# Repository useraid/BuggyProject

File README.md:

# Buggy Project (UTA024) TIET

The files for ECED part can be [found here.](empty)

The files for CSED part can be [found here.](empty)

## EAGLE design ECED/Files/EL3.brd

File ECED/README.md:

# ECED

## Labs

Lab 1 - [Reciever](https://github.com/useraid/BuggyProject/blob/main/ECED/Files/EL1.brd)

Lab 2 - [IR Module](https://github.com/useraid/BuggyProject/blob/main/ECED/Files/EL2.brd)

Lab 3 - [Transmitter](https://github.com/useraid/BuggyProject/blob/main/ECED/Files/EL3.brd)

## Challenges

[Bronze Challenge](./Bronze.ino)

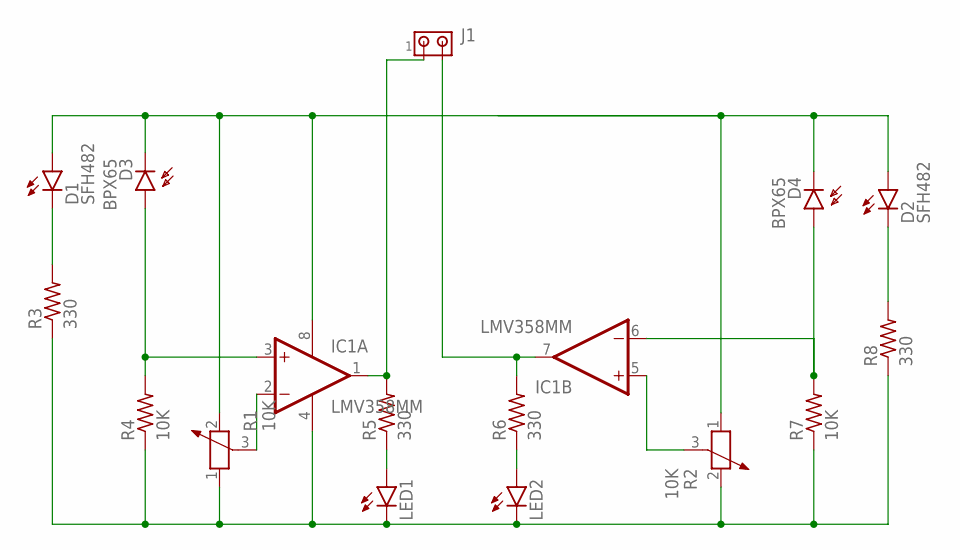
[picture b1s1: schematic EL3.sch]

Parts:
D1, D2: SFH482
D3, D4: BPX65
IC1: LMV358MM; MSOP08
J1: MTA02-100; 10X02MTA
LED1, LED2: LED3MM
R1, R2: 10K; PT-10
R3, R5, R6, R8: 330; 0204/5
R4, R7: 10K; 0204/5

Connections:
unnamed: LED2.A, R6.1
unnamed: IC1.4 (V-), LED1.K (C), LED2.K (C), R1.1, R2.2, R3.1, R4.1, R7.1, R8.1
unnamed: D4.A, IC1.6 (-IN), R7.2
unnamed: D2.K (C), R8.2
unnamed: D1.A, D2.A, D3.K (C), D4.K (C), IC1.8 (V+), R1.2, R2.1
unnamed: IC1.5 (+IN), R2.3
unnamed: IC1.7 (OUT), J1.2, R6.2
unnamed: IC1.1 (OUT), J1.1, R5.2
unnamed: LED1.A, R5.1
unnamed: D1.K (C), R3.2
unnamed: IC1.2 (-IN), R1.3
unnamed: D3.A, IC1.3 (+IN), R4.2

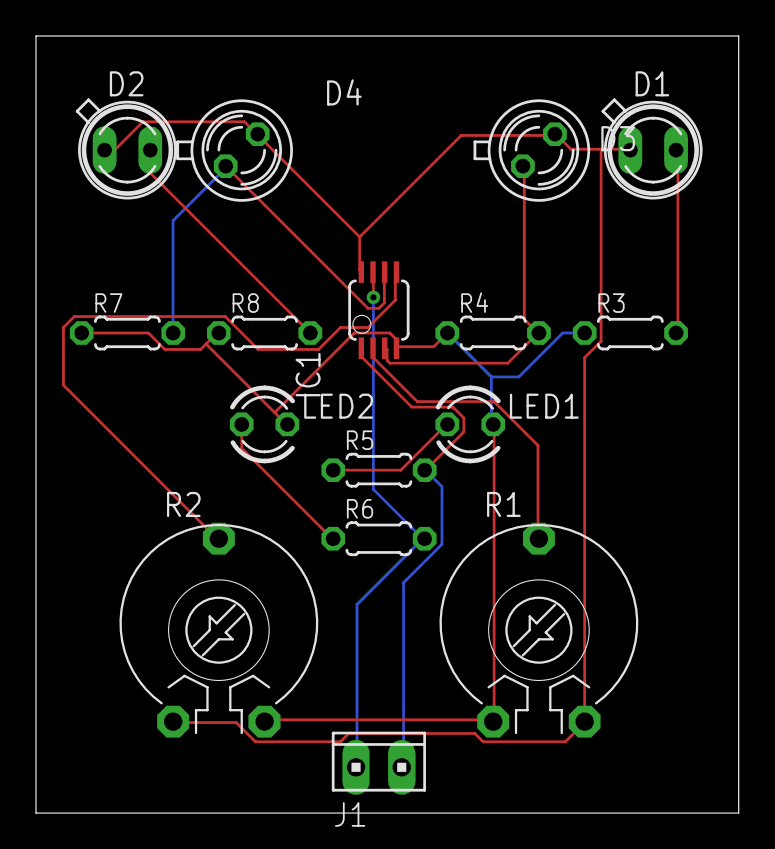
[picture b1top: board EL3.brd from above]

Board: 2 copper layers, 39.0 x 43.2 mm, 16 parts (0 on the bottom side), 12 nets.

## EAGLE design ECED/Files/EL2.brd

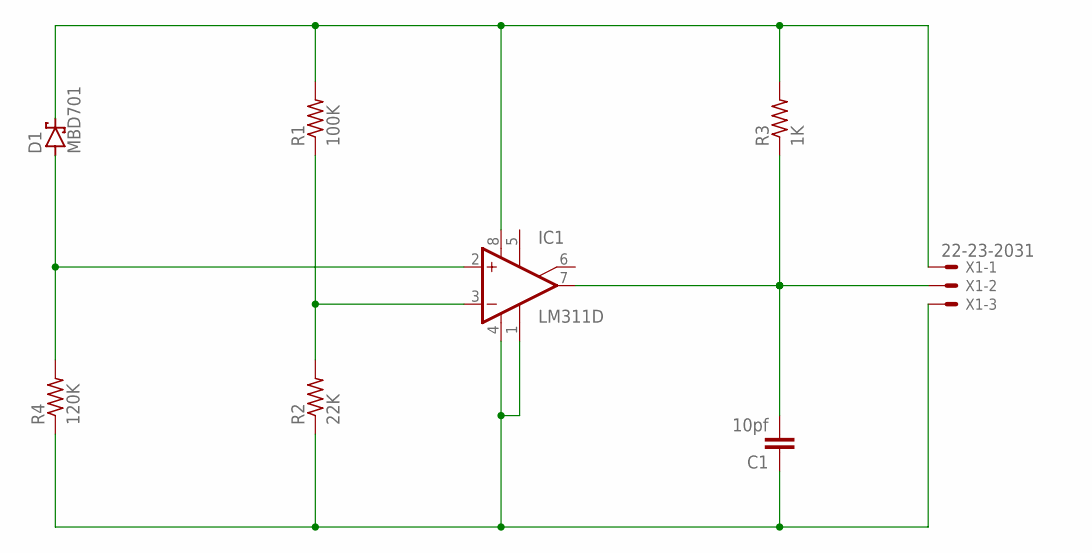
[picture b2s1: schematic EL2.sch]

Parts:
C1: 10pf; C0603
D1: MBD701; TO92H
IC1: LM311D; SO08
R1: 100K; R0603
R2: 22K; R0603
R3: 1K; R0603
R4: 120K; R0603
X1: 22-23-2031

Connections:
unnamed: D1.2 (C), IC1.8 (V+), R1.2, R3.2, X1.1
unnamed: C1.1, IC1.1 (GND), IC1.4 (V-), R2.1, R4.1, X1.3
unnamed: D1.1 (A), IC1.2 (+IN), R4.2
unnamed: IC1.3 (-IN), R1.1, R2.2
unnamed: C1.2, IC1.7 (OUT), R3.1, X1.2

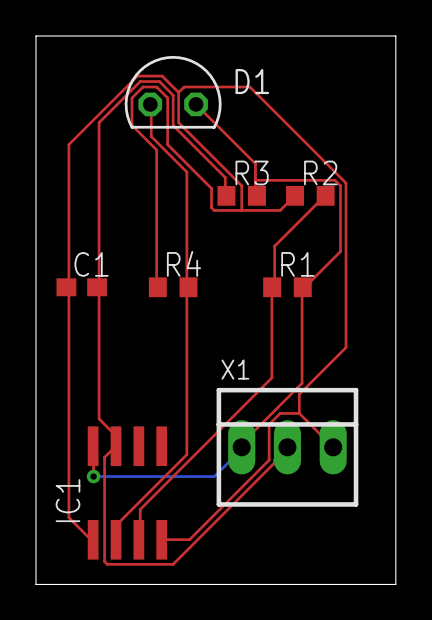
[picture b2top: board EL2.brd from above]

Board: 2 copper layers, 20.0 x 30.5 mm, 8 parts (0 on the bottom side), 5 nets.

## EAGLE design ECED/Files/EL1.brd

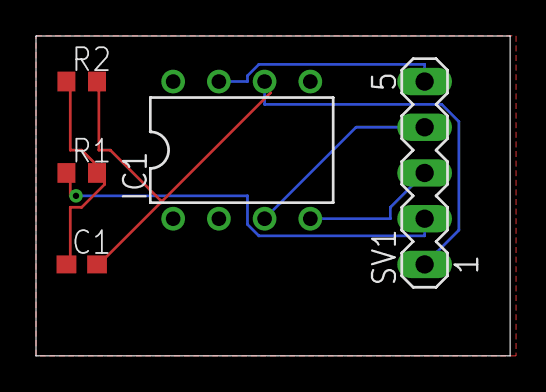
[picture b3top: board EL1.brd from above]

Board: 2 copper layers, 26.3 x 17.8 mm, 5 parts (0 on the bottom side), 6 nets.

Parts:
C1: 2uF; C0603
IC1: LM741P; DIL08
R1: 1k; R0603
R2: 10k; R0603
SV1: MA05-1

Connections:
+15V: IC1.7, SV1.5
-15V: IC1.4, SV1.3
GND: IC1.3, SV1.4
unnamed: C1.1, IC1.2, R1.2, R2.1
unnamed: C1.2, IC1.6, R2.2, SV1.1
unnamed: R1.1, SV1.2

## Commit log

2022-08-05 added lab ec
2022-08-05 updated docs
2022-08-12 added CSED L1
2022-08-12 doc formatting
2022-08-12 added ec lab 3
2022-08-12 added docs
